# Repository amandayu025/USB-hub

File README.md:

# USB-hub
## Description

It's a USB hub that can be conected through a USB type-C port, expanding one USB entrance to four, two USB type-A and two USB type-C.<br>
I added my favorite Sanrio characters (My Melody, Kuromi and Cinnamoroll) to make is look cuter ^o^<br>
(This is my first PCB project, i followed Macondo's (Hackclub) guide to build it :D)

## Components

1 SL2.1S from CoreChips <br>
3 USB-C <br>
2 USB-A <br>
6 5.1K resistors <br>
11 capacitors (8 of the 1uF type and 3 of the 100nF)

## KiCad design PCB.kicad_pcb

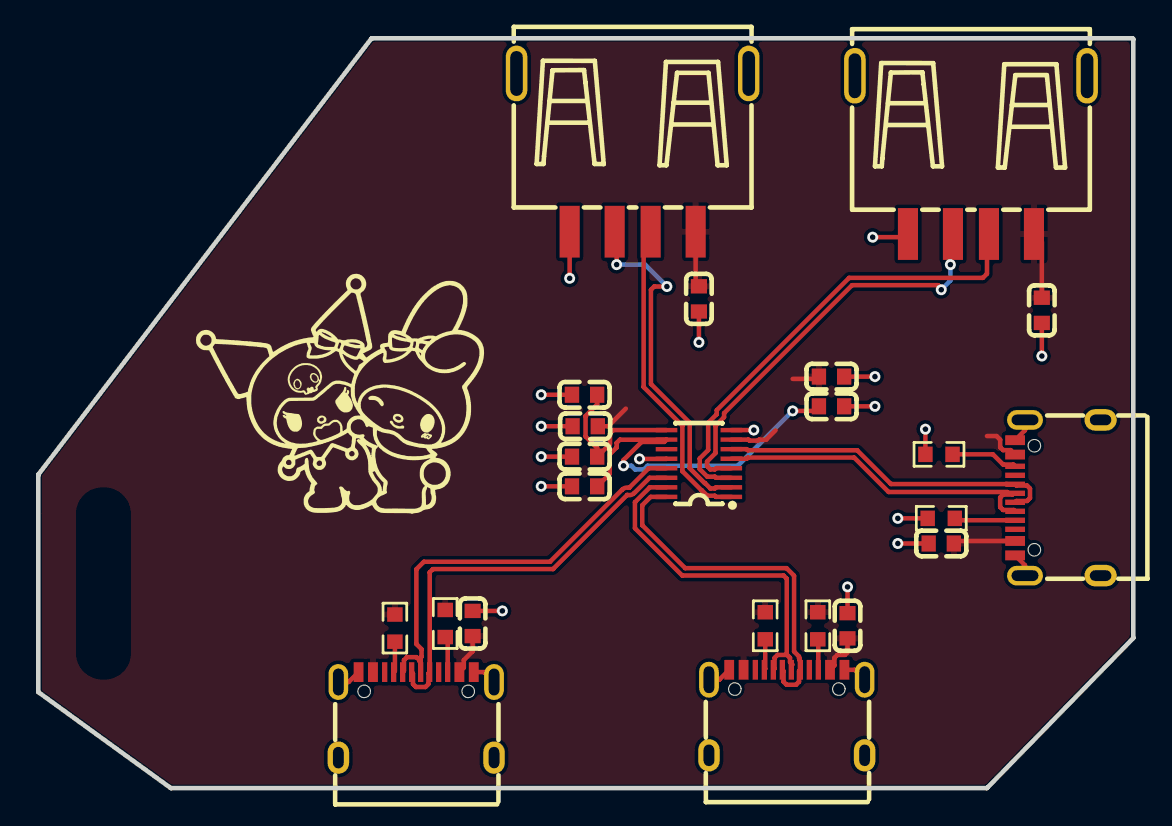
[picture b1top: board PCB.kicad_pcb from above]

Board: 2 copper layers, 60.8 x 41.7 mm, 23 parts (0 on the bottom side), 20 nets.

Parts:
C1, C2, C3, C4, C5, C6, C7, C8, C9, C10, C11: C0603
R1, R2, R3, R4, R5, R6: R0603
U1: SSOP-16_L4.6-W2.6-P0.53-LS4.0-BL
USB1, USB2, USB3: USB-C-SMD_TYPE-C-16PIN-2MD-073
USB4, USB5: USB-A-TH_10.0QHHTZB6.3

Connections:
$1N1094: R1.2, USB1.A5
$1N1099: R2.2, USB1.B5
$1N2154: R3.2, USB2.A5
$1N2189: R4.2, USB2.B5
$1N2216: R5.2, USB3.A5
$1N2251: R6.2, USB3.B5
$1N2782: C9.1, C10.1, U1.10
$1N2788: C7.1, C8.1, U1.9
+5V: C1.1, C2.1, C3.2, C4.2, C5.1, C6.1, C11.1, R3.1, R4.1, R5.1, R6.1, U1.7, USB1.A4B9, USB1.B4A9, USB2.A4B9, USB2.B4A9, USB3.A4B9, USB3.B4A9, USB4.1, USB5.1
DN: U1.5, USB1.A7, USB1.B7
DN1: U1.3, USB4.2
DN2: U1.1, USB5.2
DN3: U1.15, USB2.A7, USB2.B7
DN4: U1.13, USB3.A7, USB3.B7
DP: U1.6, USB1.A6, USB1.B6
DP1: U1.4, USB4.3
DP2: U1.2, USB5.3
DP3: U1.16, USB2.A6, USB2.B6
DP4: U1.14, USB3.A6, USB3.B6
GND: C1.2, C2.2, C3.1, C4.1, C5.2, C6.2, C7.2, C8.2, C9.2, C10.2, C11.2, R1.1, R2.1, U1.8, U1.12, USB1.13, USB1.14, USB1.A1B12, USB1.B1A12, USB2.13, USB2.14, USB2.A1B12, USB2.B1A12, USB3.13, USB3.14, USB3.A1B12, USB3.B1A12, USB4.4, USB4.5, USB4.6, USB5.4, USB5.5, USB5.6

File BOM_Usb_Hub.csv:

"ID","Name","Designator","Footprint","Quantity","Manufacturer Part","Manufacturer","Supplier","Supplier Part"
"1","SL2.1s","U1","SSOP-16_L4.6-W2.6-P0.53-LS4.0-BL","1","SL2.1s","CoreChips(和芯润德)","LCSC","C2684433"
"2","TYPE-C 16PIN 2MD(073)","USB1,USB2,USB3","USB-C-SMD_TYPE-C-16PIN-2MD-073","3","TYPE-C 16PIN 2MD(073)","SHOU HAN(首韩)","LCSC","C2765186"
"3","10.0 QHHTZB6.3","USB4,USB5","USB-A-TH_10.0QHHTZB6.3","2","10.0 QHHTZB6.3","SHOU HAN(首韩)","LCSC","C668591"
"4","5.1K","R1,R2,R3,R4,R5,R6","R0603","6","","","",""
"5","1 uF","C1,C2,C3,C4,C5,C7,C9,C11","C0603","8","","","",""
"6","100nF","C6,C8,C10","C0603","3","","","",""
